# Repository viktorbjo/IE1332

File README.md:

# IE1332-Utveckling-av-elektronikprodukter

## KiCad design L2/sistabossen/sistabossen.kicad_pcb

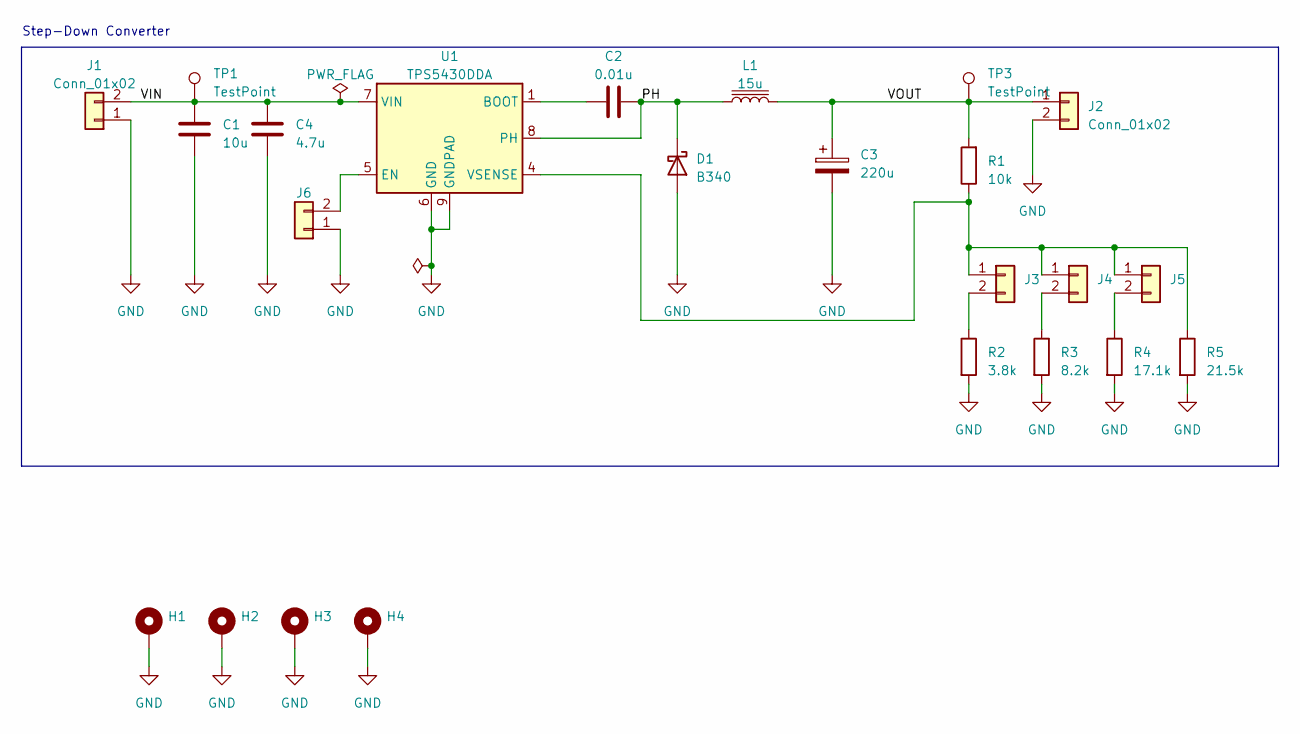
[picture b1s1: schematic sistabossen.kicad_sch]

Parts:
C1: 10u; C_0805_2012Metric_Pad1.18x1.45mm_HandSolder
C2: 0.01u; C_0805_2012Metric_Pad1.18x1.45mm_HandSolder
C3: 220u; CP_Elec_6.3x5.9
C4: 4.7u; C_0805_2012Metric_Pad1.18x1.45mm_HandSolder
D1: B340; D_SMC
H1, H2, H3, H4: MountingHole_Pad; MountingHole_3.2mm_M3_Pad_Via
J1, J2: Conn_01x02; TerminalBlock_Phoenix_MPT-0,5-2-2.54_1x02_P2.54mm_Horizontal
J3, J4, J5, J6: Conn_01x02; PinHeader_1x02_P2.54mm_Vertical
L1: 15u; L_Wuerth_WE-PD-Typ-LS_Handsoldering
R1: 10k; R_0805_2012Metric_Pad1.20x1.40mm_HandSolder
R2: 3.8k; R_0805_2012Metric_Pad1.20x1.40mm_HandSolder
R3: 8.2k; R_0805_2012Metric_Pad1.20x1.40mm_HandSolder
R4: 17.1k; R_0805_2012Metric_Pad1.20x1.40mm_HandSolder
R5: 21.5k; R_0805_2012Metric_Pad1.20x1.40mm_HandSolder
TP1, TP3: TestPoint; TestPoint_THTPad_2.5x2.5mm_Drill1.2mm
U1: TPS5430DDA; TI_SO-PowerPAD-8_ThermalVias

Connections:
/PH: C2.2, D1.1 (K), L1.1, U1.8 (PH)
/VIN: C1.1, C4.1, J1.2, TP1.1, U1.7 (VIN)
/VOUT: C3.1, J2.1, L1.2, R1.2, TP3.1
GND: C1.2, C3.2, C4.2, D1.2 (A), H1.1, H2.1, H3.1, H4.1, J1.1, J2.2, J6.1, R2.2, R3.2, R4.2, R5.2, U1.6 (GND), U1.9 (GNDPAD)
unnamed: J3.1, J4.1, J5.1, R1.1, R5.1, U1.4 (VSENSE)
unnamed: J3.2, R2.1
unnamed: J4.2, R3.1
unnamed: J5.2, R4.1
unnamed: J6.2, U1.5 (EN)
unnamed: C2.1, U1.1 (BOOT)

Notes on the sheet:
Step-Down Converter

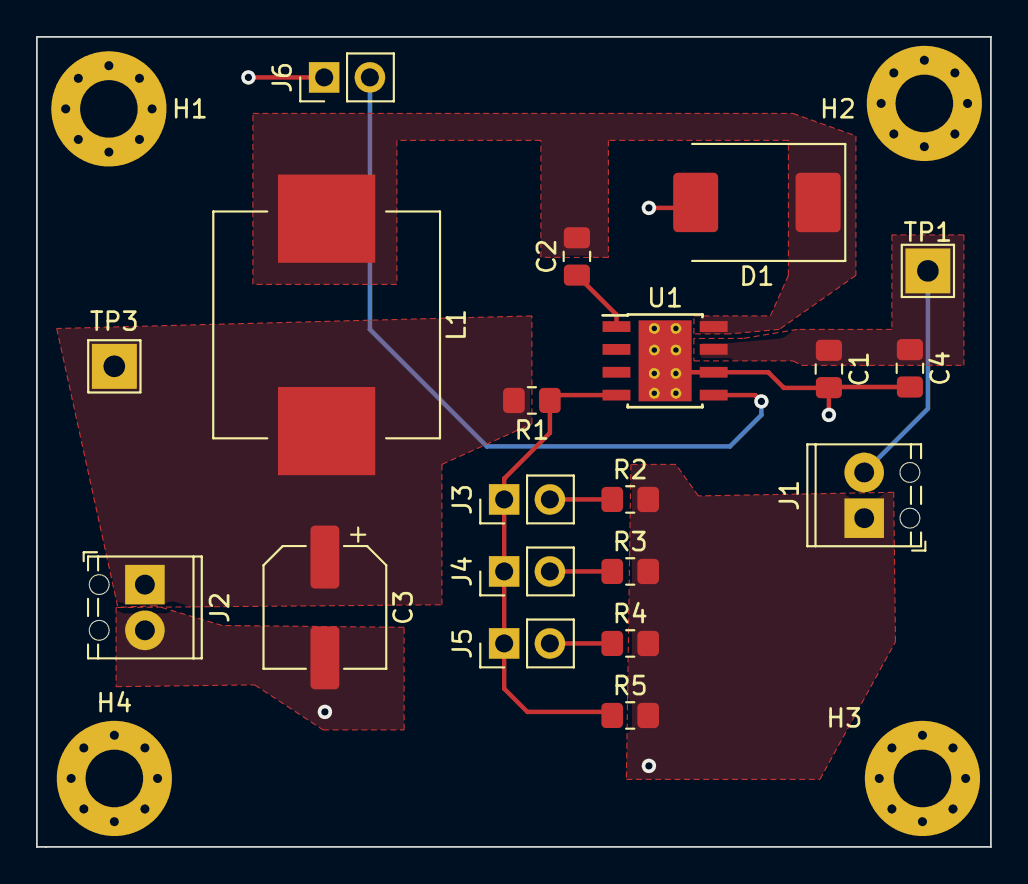
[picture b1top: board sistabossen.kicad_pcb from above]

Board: 2 copper layers, 53.0 x 45.0 mm, 24 parts (0 on the bottom side), 10 nets.

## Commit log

2023-04-06 test
2023-04-06 seminar 1
2023-04-10 labb 2 kicad
2023-04-10 yesbox
2023-04-11 gerbersssss
2023-04-13 nått?
2023-04-13 bilder
2023-04-17 laptop
2023-04-21 version 1.1
2023-04-26 bomHTML
2023-04-26 bom fil
2023-04-27 ny dator
2023-04-27 namn
2023-04-27 seminarie 2
2023-04-28 sem2 update
2023-04-28 sista!!!
2023-05-05 document
2023-05-09 frågor
2023-05-10 presentation
2023-05-17 labbrapoort
2023-05-18 labbrapport
2023-05-18 labb pdf
2023-05-19 lituppgift
2023-05-20 instudering
2023-05-20 update labb
2023-05-20 labb igeeeeen
2023-05-30 pdf instudering
2023-06-20 sista
